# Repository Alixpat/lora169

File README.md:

# lora169

Carte LoRa 169 MHz autonome. Conformité ARCEP 2007-0689 (bande 169,4–169,475 MHz, 27 dBm p.a.r. max).

## Hardware

- **MCU** : Seeed XIAO ESP32-S3 (USB-C natif)
- **Radio** : Ebyte E22-170M30S (SX1262, IPEX), enfichable sur breakout démontable
- **Antenne** : Ebyte TX170-JKD-20 (3 dBi, fouet 200 mm), via pigtail U.FL → SMA bulkhead
- **Boîtier** : impression 3D paramétrique

## État du projet

| Pièce | Source | DRC / vérif | Statut |
|-------|--------|-------------|--------|
| Carte mère (80 × 55 mm) | `hardware/lora169.kicad_*` | 0 erreur | Commandée JLCPCB |
| Breakout E22 (40,6 × 46,3 mm) | `hardware/breakout-e22/*.kicad_*` | 0 erreur | Commandé JLCPCB |
| Boîtier 3D (94 × 69 × 32,6 mm) | `enclosure/boitier-lora169.scad` | — | Commandé JLC3DP |

## Structure

```
docs/datasheets/        Datasheets PDF (E22, SX1262, AN Semtech)
hardware/               Projet KiCad carte mère
hardware/libs/          Symboles + empreintes vendorisés (Seeed, Ebyte)
hardware/breakout-e22/  Projet KiCad de la carte fille E22
enclosure/              Boîtier OpenSCAD paramétrique
```

## Outils (Debian 13)

```bash
sudo apt install kicad kicad-libraries kicad-symbols kicad-footprints kicad-packages3d openscad
```

## Ouvrir le projet

`hardware/lora169.kicad_pro` (carte mère) ou `hardware/breakout-e22/breakout-e22.kicad_pro` (breakout). Les libs `Seeed_XIAO` et `Ebyte_E22` sont déjà déclarées via `${KIPRJMOD}`.

Pour le boîtier : `openscad enclosure/boitier-lora169.scad` — modifier `show_mode` (`"box"` / `"lid"` / `"assembled"` / `"exploded"`), F6, exporter en STL.

## Régénérer les Gerbers

```bash
cd hardware
kicad-cli pcb export gerbers --output fab/ \
  --layers "F.Cu,B.Cu,F.Paste,B.Paste,F.Silkscreen,B.Silkscreen,F.Mask,B.Mask,Edge.Cuts" \
  lora169.kicad_pcb
kicad-cli pcb export drill --output fab/ lora169.kicad_pcb
cd fab && python3 -m zipfile -c ../lora169-gerbers.zip *.g* *.drl
```

## Journal des commandes

| Date       | Composant                          | Qté | Source     | Sous-total | Frais (livr./douane/PayPal) | Réduction | Total   |
|------------|------------------------------------|-----|------------|-----------:|----------------------------:|----------:|--------:|
| 2026-05-01 | Seeed XIAO ESP32-S3                | 2   | AliExpress (Seeedstudio AI Hardware Store) | 15,49 € | 4,41 € | −0,87 € | 19,03 € |
| 2026-05-01 | Ebyte E22-170M30S                  | 2   | AliExpress (Boutique officielle EBYTE) | 13,78 € | 4,17 € | −0,77 € | 17,18 € |
| 2026-05-03 | PCB carte mère + breakout + 2 boîtiers 3D (groupé W2026050322580094) | 5+5+2+2 | JLCPCB / JLC3DP | 14,64 € | 15,08 € | −8,52 € | 21,20 € |

**Total engagé : 57,41 €**

À commander : antenne Ebyte TX170-JKD-20 (CDSENET, ~13 €), condensateurs SMD 0805 100 nF + 10 µF (Supplier of electronic components, ~2 €), pin headers + embases femelles 1×40 (~2 €). Pigtail U.FL → SMA femelle bulkhead disponible en stock.

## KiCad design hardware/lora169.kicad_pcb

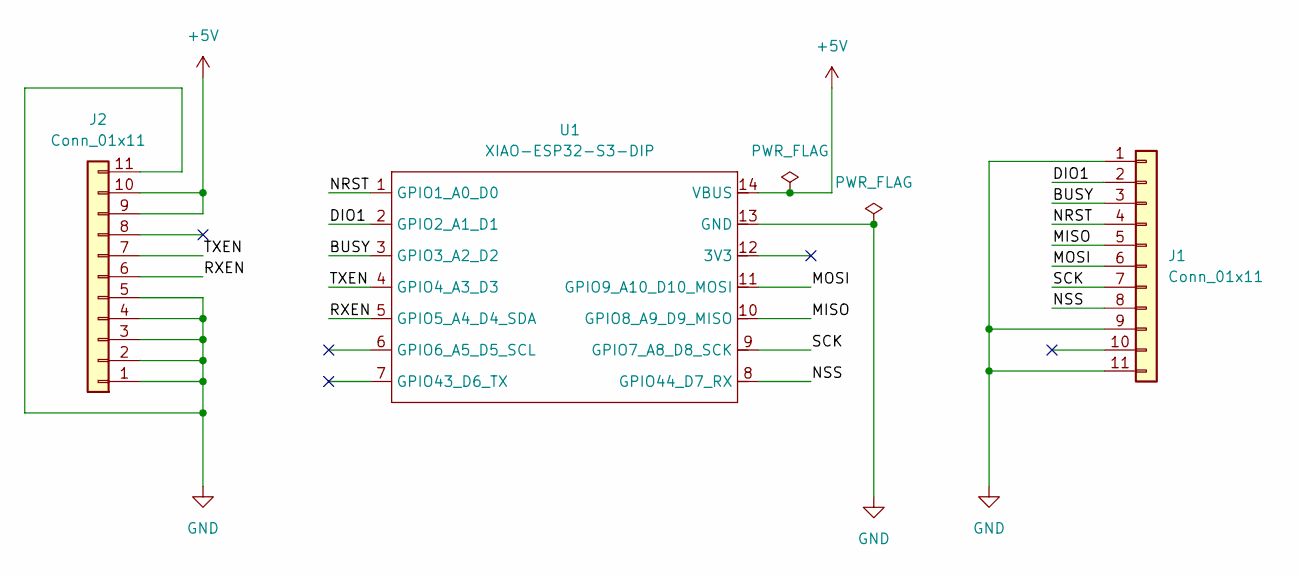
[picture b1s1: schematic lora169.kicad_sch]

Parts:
J1, J2: Conn_01x11; PinSocket_1x11_P2.54mm_Vertical
U1: XIAO-ESP32-S3-DIP

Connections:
+5V: J2.9, J2.10, U1.14 (VBUS)
/BUSY: J1.3, U1.3 (GPIO3_A2_D2)
/DIO1: J1.2, U1.2 (GPIO2_A1_D1)
/MISO: J1.5, U1.10 (GPIO8_A9_D9_MISO)
/MOSI: J1.6, U1.11 (GPIO9_A10_D10_MOSI)
/NRST: J1.4, U1.1 (GPIO1_A0_D0)
/NSS: J1.8, U1.8 (GPIO44_D7_RX)
/RXEN: J2.6, U1.5 (GPIO5_A4_D4_SDA)
/SCK: J1.7, U1.9 (GPIO7_A8_D8_SCK)
/TXEN: J2.7, U1.4 (GPIO4_A3_D3)
GND: J1.1, J1.9, J1.11, J2.1, J2.2, J2.3, J2.4, J2.5, J2.11, U1.13 (GND)

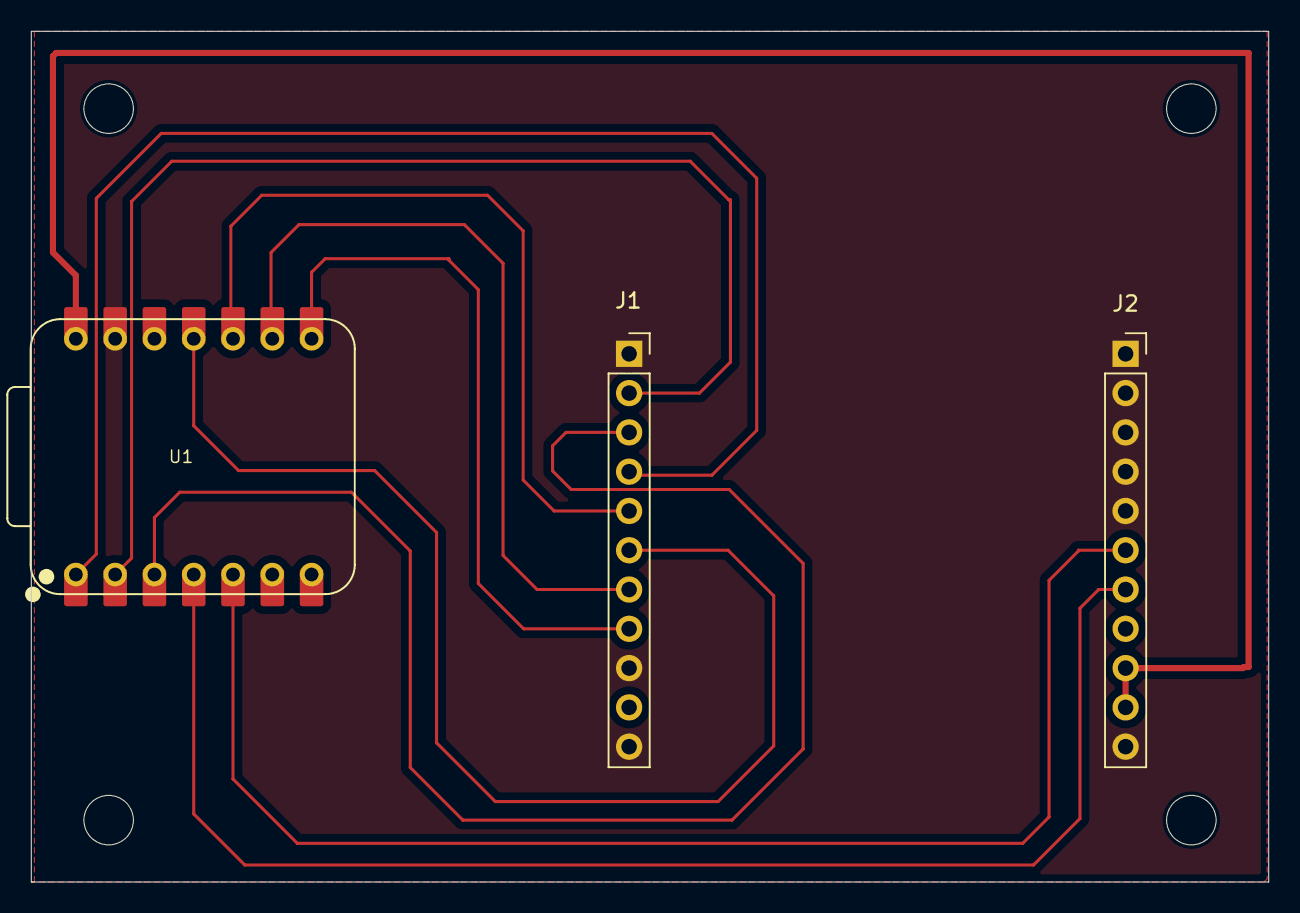
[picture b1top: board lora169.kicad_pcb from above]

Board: 2 copper layers, 80.0 x 55.0 mm, 3 parts (0 on the bottom side), 11 nets.

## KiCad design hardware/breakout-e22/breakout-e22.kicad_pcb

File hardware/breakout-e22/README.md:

# Breakout E22 (carte fille)

Carte adaptatrice qui transforme le module Ebyte E22-170M30S (SMD, pads
en bord) en module DIP enfichable via deux pin headers 1×11 broches au
pas 2,54 mm. Permet de changer de fréquence (170 / 400 / 900 MHz) sur
la carte mère sans dessouder.

## Conception

Design propre fait pour ce projet, avec :

- 1× module E22-xxxM30S (mécanique commune à 170/400/900 MHz)
- 2× condensateurs de découplage 100 nF + 10 µF (céramique X7R 0805)
  au plus près des pins VCC, pour absorber le pic TX 30 dBm (~620 mA)
- 2× pin headers 1×11 broches au pas 2,54 mm sur les bords longs
- VCC alimenté en 5 V depuis VBUS du XIAO côté carte mère, pour
  permettre la pleine puissance 30 dBm hardware
- Plan de masse continu sur la face arrière

## Caractéristiques techniques

- Format PCB : **40,6 × 46,3 mm** (compact, à peine plus large que
  le module E22 lui-même de 24 × 38,5 mm)
- Espacement entre les deux pin headers J1/J2 : **32,1 mm** centre à
  centre — à respecter sur la carte mère (embases femelles 1×11)
- Pistes signal en 0,2 mm, piste alim +5V en 0,4 mm pour absorber le
  pic 620 mA en TX 30 dBm
- Pads GND en pleine connexion à la zone GND (sans thermal relief)
  pour minimiser l'inductance de retour

## Valeurs de découplage — sources

Le combo **100 nF + 10 µF céramique 0805** est validé par la pratique
de plusieurs designs publics éprouvés à 30 dBm voire 33 dBm :

- [eigenlucy/e22900m30s](https://github.com/eigenlucy/e22900m30s) :
  E22-900M30S, alim 5 V, 10 µF (0805) + 100 nF (0402)
- [KaliAssistant/MeshAdv_piHAT_v2](https://github.com/KaliAssistant/MeshAdv_piHAT_v2) :
  E22-900M33S (33 dBm = 2 W !), 10 µF + 100 nF répartis sur les rails
- [andrew-moroz/xiao-ble-pcb](https://github.com/andrew-moroz/xiao-ble-pcb) :
  E22-900M30S, MiniBoost 5 V + 100 µF buffering en sortie

Ni la datasheet E22 ni les notes Semtech (AN1200.37, AN1200.40) ne
donnent de valeurs explicites pour le découplage externe d'un module
E22 fini — la datasheet recommande juste un « external ceramic filter
capacitor ». Les 100 nF + 10 µF sont donc retenus comme convention
d'industrie validée empiriquement.

## Mapping J1 / J2 (côté carte mère)

| Pin header | Broche | Signal   | Pad E22 |
|------------|--------|----------|---------|
| J2         | 1-5, 11| GND      | 1-5, 11 |
| J2         | 6      | RXEN     | 6       |
| J2         | 7      | TXEN     | 7       |
| J2         | 8      | NC (DIO2)| 8       |
| J2         | 9-10   | +5V (VCC)| 9-10    |
| J1         | 1, 9, 11| GND     | 12, 20, 22 |
| J1         | 2      | DIO1     | 13      |
| J1         | 3      | BUSY     | 14      |
| J1         | 4      | NRST     | 15      |
| J1         | 5      | MISO     | 16      |
| J1         | 6      | MOSI     | 17      |
| J1         | 7      | SCK      | 18      |
| J1         | 8      | NSS      | 19      |
| J1         | 10     | NC (ANT) | 21 (sortie RF, non utilisée en IPEX) |

## Statut

- DRC : 0 erreur, 0 unconnected
- Gerbers générés : `breakout-e22-gerbers.zip`
- Prêt à fabriquer chez JLCPCB / PCBWay

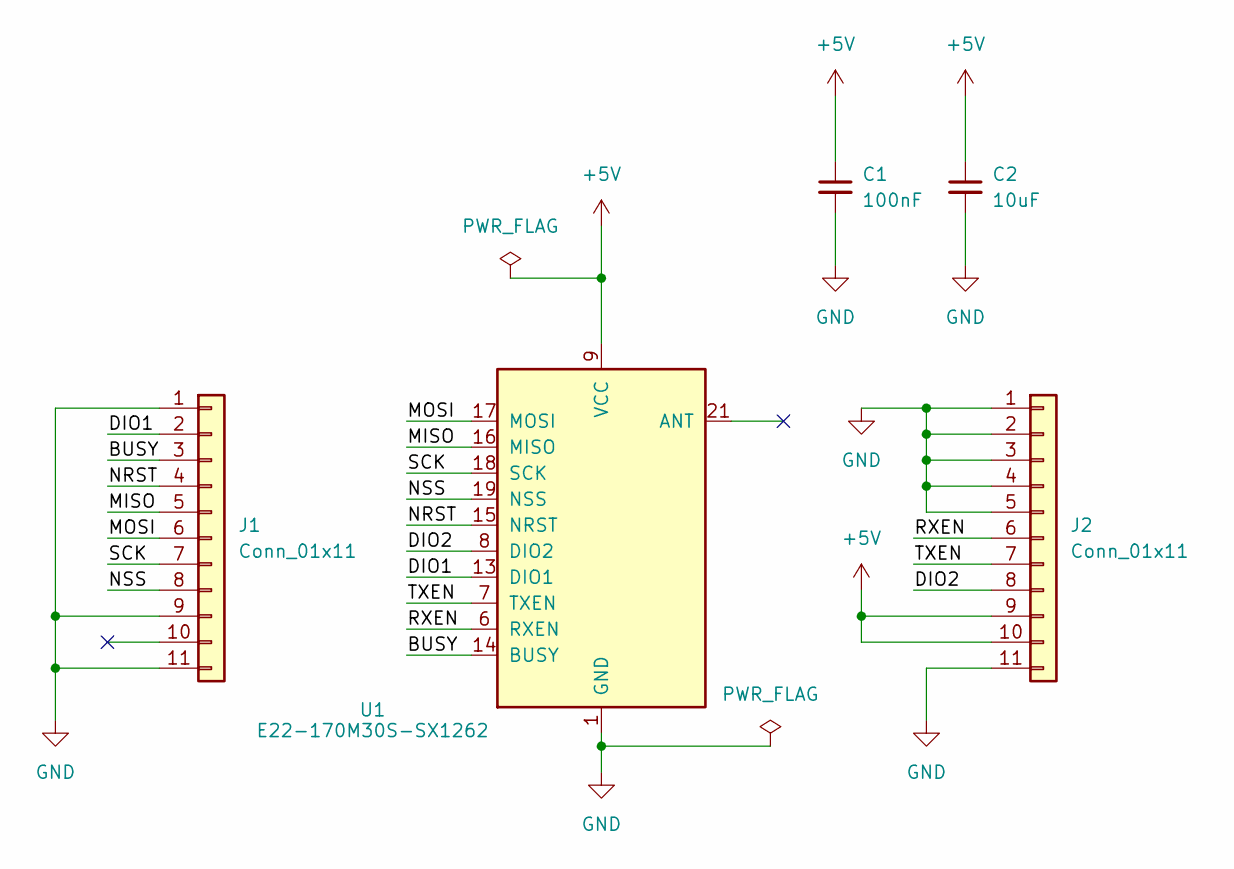
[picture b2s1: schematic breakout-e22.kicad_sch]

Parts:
C1: 100nF; C_0805_2012Metric
C2: 10uF; C_0805_2012Metric
J1, J2: Conn_01x11; PinHeader_1x11_P2.54mm_Vertical
U1: E22-170M30S-SX1262

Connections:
+5V: C1.1, C2.1, J2.9, J2.10, U1.9 (VCC), U1.10 (VCC)
/BUSY: J1.3, U1.14 (BUSY)
/DIO1: J1.2, U1.13 (DIO1)
/DIO2: J2.8, U1.8 (DIO2)
/MISO: J1.5, U1.16 (MISO)
/MOSI: J1.6, U1.17 (MOSI)
/NRST: J1.4, U1.15 (NRST)
/NSS: J1.8, U1.19 (NSS)
/RXEN: J2.6, U1.6 (RXEN)
/SCK: J1.7, U1.18 (SCK)
/TXEN: J2.7, U1.7 (TXEN)
GND: C1.2, C2.2, J1.1, J1.9, J1.11, J2.1, J2.2, J2.3, J2.4, J2.5, J2.11, U1.1 (GND), U1.2 (GND), U1.3 (GND), U1.4 (GND), U1.5 (GND), U1.11 (GND), U1.12 (GND), U1.20 (GND), U1.22 (GND)

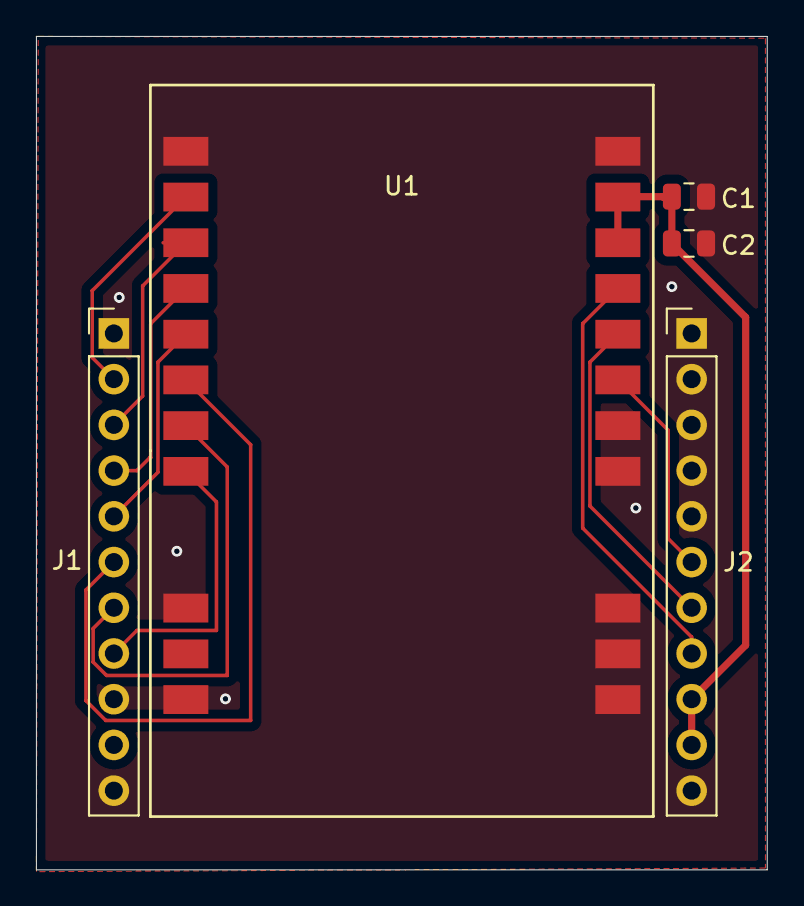
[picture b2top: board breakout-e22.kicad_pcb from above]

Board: 2 copper layers, 40.6 x 46.3 mm, 5 parts (0 on the bottom side), 12 nets.
